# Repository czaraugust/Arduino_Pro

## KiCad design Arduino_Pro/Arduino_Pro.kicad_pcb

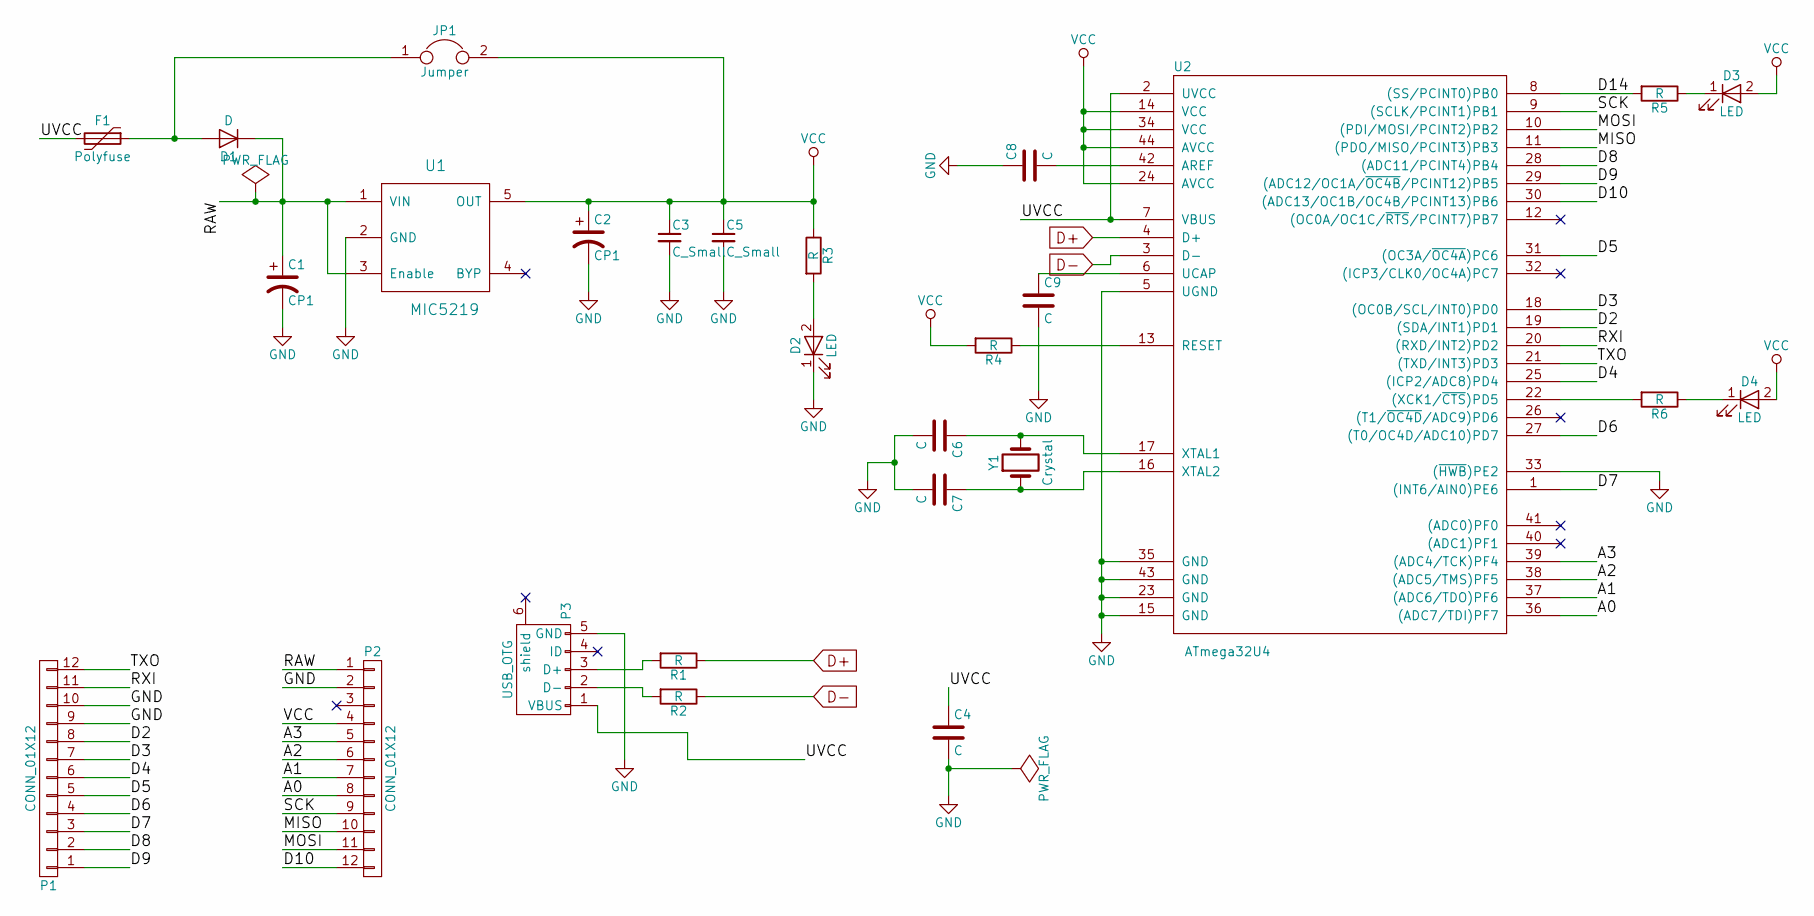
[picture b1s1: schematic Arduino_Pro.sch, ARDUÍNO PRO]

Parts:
C1, C2: CP1; C_0603
C3, C5: C_Small; C_0603
C4, C6, C7, C8, C9: C; C_0603
D1: D; D_0603
D2, D3, D4: LED; LED_0603
F1: Polyfuse; Fuse_SMD1206_Reflow
JP1: Jumper; Pin_Header_Straight_1x02_Pitch1.27mm
P1, P2: CONN_01X12; Socket_Strip_Straight_1x12_Pitch1.27mm
P3: USB_OTG; USB_Micro-B_10103594-0001LF
R1, R2, R3, R4, R5, R6: R; R_0603
U1: MIC5219; SOT-23-5
U2: ATmega32U4; LQFP-44_10x10mm_Pitch0.8mm
Y1: Crystal; Crystal_SMD_0603-2pin_6.0x3.5mm

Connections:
/A0: P2.8, U2.36 ((ADC7/TDI)PF7)
/A1: P2.7, U2.37 ((ADC6/TDO)PF6)
/A2: P2.6, U2.38 ((ADC5/TMS)PF5)
/A3: P2.5, U2.39 ((ADC4/TCK)PF4)
/D2: P1.8, U2.19 ((SDA/INT1)PD1)
/D3: P1.7, U2.18 ((OC0B/SCL/INT0)PD0)
/D4: P1.6, U2.25 ((ICP2/ADC8)PD4)
/D5: P1.5, U2.31 ((OC3A/~OC4A~)PC6)
/D6: P1.4, U2.27 ((T0/OC4D/ADC10)PD7)
/D7: P1.3, U2.1 ((INT6/AIN0)PE6)
/D8: P1.2, U2.28 ((ADC11/PCINT4)PB4)
/D9: P1.1, U2.29 ((ADC12/OC1A/~OC4B~/PCINT12)PB5)
/D10: P2.12, U2.30 ((ADC13/OC1B/OC4B/PCINT13)PB6)
/D14: R5.2, U2.8 ((SS/PCINT0)PB0)
/MISO: P2.10, U2.11 ((PDO/MISO/PCINT3)PB3)
/MOSI: P2.11, U2.10 ((PDI/MOSI/PCINT2)PB2)
/RAW: C1.1, D1.1 (K), P2.1, U1.1 (VIN), U1.3 (Enable)
/RXI: P1.11, U2.20 ((RXD/INT2)PD2)
/SCK: P2.9, U2.9 ((SCLK/PCINT1)PB1)
/TXO: P1.12, U2.21 ((TXD/INT3)PD3)
/UVCC: C4.1, F1.2, P3.1 (VBUS), U2.2 (UVCC), U2.7 (VBUS)
D+: R1.1, U2.4 (D+)
D-: R2.1, U2.3 (D-)
GND: C1.2, C2.2, C3.2, C4.2, C5.2, C6.2, C7.2, C8.1, C9.2, D2.1 (K), P1.9, P1.10, P2.2, P3.5 (GND), U1.2 (GND), U2.5 (UGND), U2.15 (GND), U2.23 (GND), U2.33 ((~HWB~)PE2), U2.35 (GND), U2.43 (GND)
unnamed: C6.1, U2.17 (XTAL1), Y1.2
unnamed: C7.1, U2.16 (XTAL2), Y1.1
unnamed: C8.2, U2.42 (AREF)
unnamed: C9.1, U2.6 (UCAP)
unnamed: D1.2 (A), F1.1, JP1.1
unnamed: D2.2 (A), R3.2
unnamed: D3.1 (K), R5.1
unnamed: D4.1 (K), R6.1
unnamed: P3.2 (D-), R2.2
unnamed: P3.3 (D+), R1.2
unnamed: R4.1, U2.13 (RESET)
unnamed: R6.2, U2.22 ((XCK1/~CTS~)PD5)
VCC: C2.1, C3.1, C5.1, D3.2 (A), D4.2 (A), JP1.2, P2.4, R3.1, R4.2, U1.5 (OUT), U2.14 (VCC), U2.24 (AVCC), U2.34 (VCC), U2.44 (AVCC)

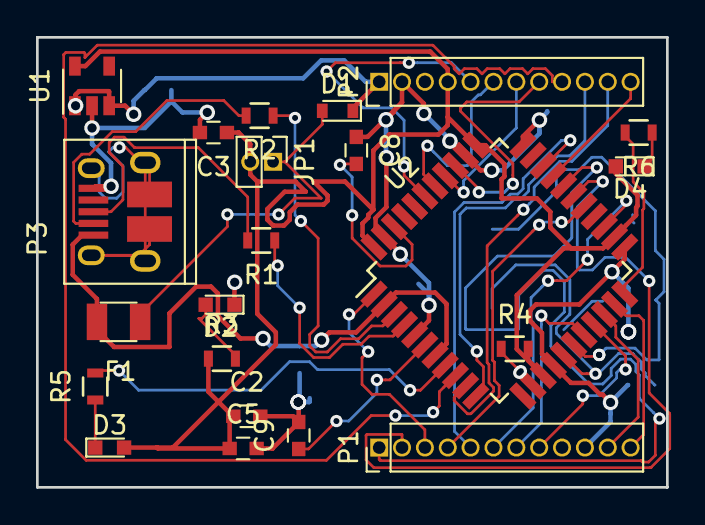
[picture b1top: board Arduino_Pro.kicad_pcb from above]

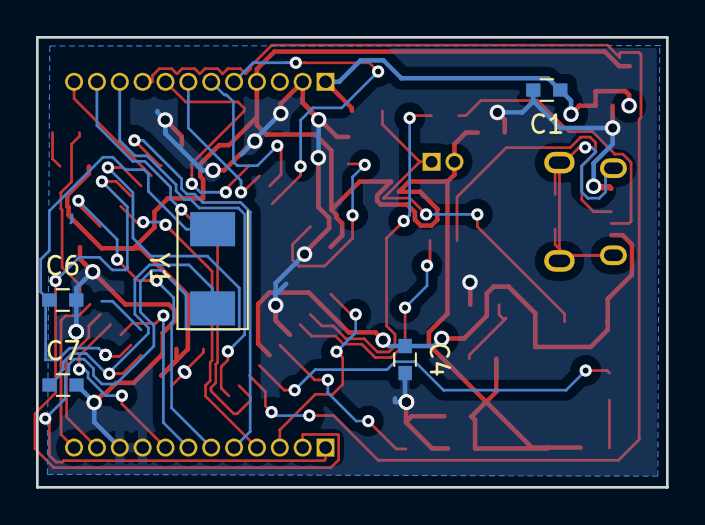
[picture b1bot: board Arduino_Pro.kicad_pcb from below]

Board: 2 copper layers, 35.0 x 25.0 mm, 27 parts (5 on the bottom side), 37 nets.

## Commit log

2017-02-17 Iniciando
